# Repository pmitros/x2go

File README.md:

x2go is a project to develop a low-cost platform for use of edX in
off-line settings.

Installing Open edX on the Intel NUC:

* Step 1: [Configure the BIOS](https://www.intel.com/content/www/us/en/support/boards-and-kits/000022600.html)
* Step 2: Download [Ubuntu 16.04 64 bit server](http://releases.ubuntu.com/16.04/). dd it to a USB stick, and install it
* Step 3: Install [Open edX](https://openedx.atlassian.net/wiki/display/OpenOPS/Native+Open+edX+Ubuntu+16.04+64+bit+Installation)
* Step 4: Install extra configuration from x2go configuration `/ansible-playbook local.yml -i '127.0.0.1,' -c local -e`
* Step 5: Create an account (via web interface), and make it into an active superuser:

     #mysql
     use edxapp
     update auth_user set is_active=1, is_staff=1, is_superuser=1 where username='pmitros';

* Step 6: Install x2go packages
* Step 7: Load courses

This project has been through a few reboots. See version history if
you care.

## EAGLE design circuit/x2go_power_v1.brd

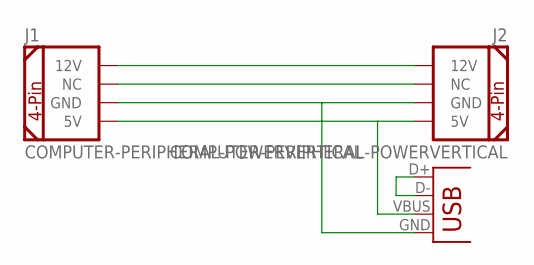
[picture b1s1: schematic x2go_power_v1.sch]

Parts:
J1, J2: COMPUTER-PERIPHERAL-POWERVERTICAL; COMPUTER-PERIPHERAL-POWER
JP1: USB-A-S

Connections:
unnamed: J1.12V, J2.12V
unnamed: J1.NC, J2.NC
unnamed: J1.GND, J2.GND, JP1.GND
unnamed: J1.5V, J2.5V, JP1.VBUS
unnamed: JP1.D+, JP1.D-

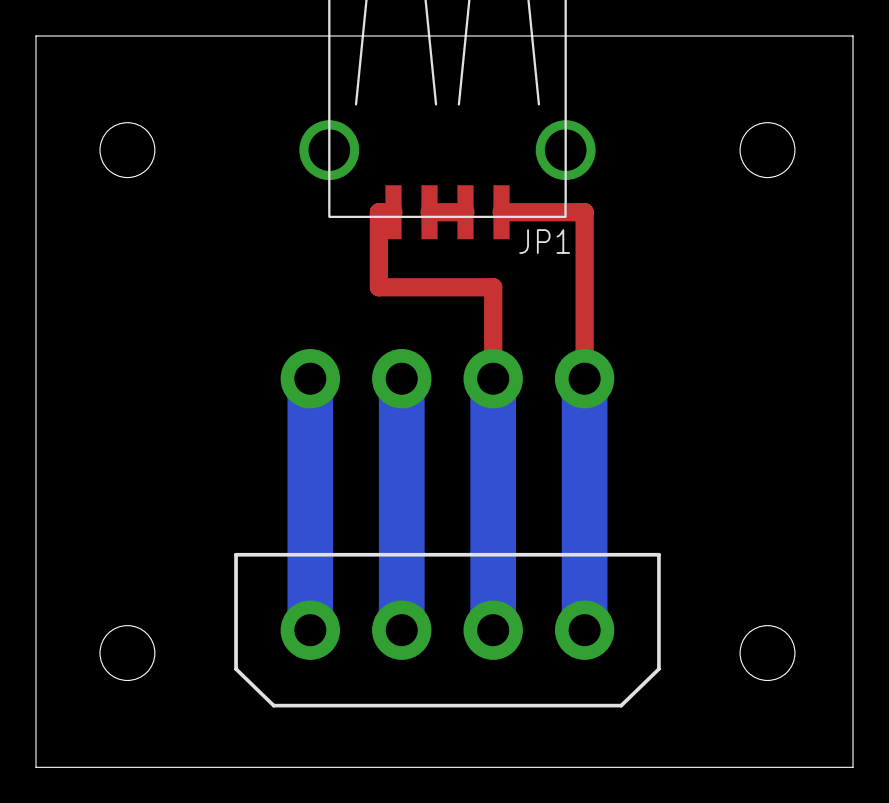
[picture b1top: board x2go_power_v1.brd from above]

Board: 2 copper layers, 45.4 x 40.6 mm, 3 parts (1 on the bottom side), 5 nets.

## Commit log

2015-01-25 empty power panel templates for cutting new boxes.
2017-07-11 Reboot of project for October deploy
2017-07-11 Install edX script
2017-07-13 Working edx platform
2017-09-13 Scripts
2017-09-13 sources.list
2017-09-19 Starting work on offline server

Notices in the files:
parts and their libraries:
SparkFun-Connectors: Licensing: CC v3.0 Share-Alike You are welcome to use this library for commercial purposes.
